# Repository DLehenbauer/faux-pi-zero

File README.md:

# Faux Pi Zero

Open hardware RP2040 dev board in a Raspberry Pi Zero compatible form factor.  Includes Mini HDMI (via [bitbanged DVI](https://github.com/Wren6991/PicoDVI)) and microSD.

## Description

This board aids with migrating a project from the Pi Zero to the RP2040 while retaining the option of moving back to the Pi Zero in the future.  It has the same footprint as the Pi Zero and a partially compatible [pinout](#pinout), making it convenient to support both the RP2040 and Pi Zero in the same design.

## Status

Works, but 1 of 2 boards received by JLCPCB had a solder bridge on the RP2040.  Looking at JLCPCB's EasyEDA footprints, it looks like JLCPCB used longer pads for the RP2040.  I'd recommend using a custom footprint and extending the pads, which hopefully will avoid defects.

A couple other things I'd change in retrospect:
* Expose UART TX/RX on the debug header and reorder pins so you can plug a [picoprobe](https://github.com/raspberrypi/picoprobe) into the board w/o wires.
* Remove the hacky activity LED from the microSD since [the lib](https://github.com/carlk3/no-OS-FatFS-SD-SPI-RPi-Pico) already blinks GP25.
* Try for a 2 layer board to reduce cost
* Reduce buttons to 6 x 3.5 and maybe try to squeeze in an optional wireless module

DVI and microSD both appear to work with a basic test.  I've exercised DVI, USB (host), SPI1, and the debug header quite a bit (all good).  Other functionality is either lightly tested or untested.

## Features

* Compatible footprint:
  * Mini HDMI (via [bitbanged DVI](https://github.com/Wren6991/PicoDVI))
  * Micro SD (via SPI mode.  Cards must be <2TB)
  * Micro USB
  * Power (via Micro USB)
* Partially compatible [pinout](#pinout)
* 16MB Flash
* Green status LED on GP25 (same as Pico)
* Red SD activity LED on GP9
* BOOTSEL and RESET buttons
* SWD Header

## Pinout

See [schematic](#schematic) for more details.

### Mapping from Pi Zero to Faux Px Zero

Pi Pin | Pico Pin | Pi GPIO | Pico GP | Function | Notes
-|-|-|-|-|-
1, 17 | 36 |  | 3V3 (Out) |  |
2, 4 | 39 |  | VSYS |  |
2, 4 | 40 |  | VBUS |  |
3 | 4 | GPIO 02 | GP 02 | I2C_SDA |
5 | 5 | GPIO 03 | GP 03 | I2C_SCL |
6, 9, 14, 20, 25, 30, 34, 39 | 3, 8, 13, 18, 23, 28, 33, 38, DBG-2 |  | GND |  |
7 |  | GPIO 04 | GP 24 |  |
8 | 1 | GPIO 14 | GP 00 | UART0 TX |
10 | 2 | GPIO 15 | GP 01 | UART0 RX |
11 | 12 | GPIO 17 | GP 09 | SD_CSn | Can be used as GP with SD card removed.  Note 10k pullup.
12 | 17 | GPIO 18 | GP 13 | SPI1_CSn | Can be used to share SPI1 with SD card.
13 | 11 | GPIO 27 | GP 08 | SD_DET | Can be used as GP with SD card removed.
15 | 14 | GPIO 22 | GP 10 | DVI_CEC | DVI_CEC when JP3 closed.  See [schematic](#schematic).
16 | 15 | GPIO 23 | GP 11 |  |
18 | DBG-3 | GPIO 24 | SWD |  |
19 | 6/10 | GPIO 10 | GP 04/07 | SPI0_RX/TX | Select [controller](https://www.oshwa.org/a-resolution-to-redefine-spi-signal-names/) or [peripheral](https://www.oshwa.org/a-resolution-to-redefine-spi-signal-names/) via JP1 and JP2.  See [schematic](#schematic).
21 | 10/6 | GPIO 09 | GP 07/04 | SPI0_TX/RX | Select [controller](https://www.oshwa.org/a-resolution-to-redefine-spi-signal-names/) or [peripheral](https://www.oshwa.org/a-resolution-to-redefine-spi-signal-names/) via JP1 and JP2.  See [schematic](#schematic).
22 | DBG-1 | GPIO 25 | SWCLK |  |
23 | 9 | GPIO 11 | GP 06 | SPI0_SCLK |
24 | 7 | GPIO 08 | GP 05 | SPI0_CSn |
26 |  | GPIO 07 |  |  |
27 | 34 | GPIO 00 | GP 28 | I2C_SCL | DVI_SDA when JP4 closed.  See [schematic](#schematic).
28 |  | GPIO 01 | GP 29 |  |
29 | 31 | GPIO 05 | GP 26 |  |
31 | 32 | GPIO 06 | GP 27 | I2C_SDA | DVI_SDA when JP5 closed.  See [schematic](#schematic).
32 |  | GPIO 12 |  |  |
33 |  | GPIO 13 |  |  |
35 | 16 | GPIO 19 | GP 12 | SPI1_RX / SD_DAT | Can be used as GP with SD card removed.  Note 10k pullup.
36 |  | GPIO 16 | BOOTSEL |  |
37 | 30 | GPIO 26 | RUN |  |
38 | 20 | GPIO 20 | GP 15 | SPI1_TX / SD_CMD | Can be used as GP with SD card removed.
40 | 19 | GPIO 21 | GP 14 | SPI1_SCLK / SD_CLK | Can be used as GP with SD card removed.
   |    |    | GP 23 | DVI_D2+ |
   |    | 21 | GP 16 | DVI_CK- |
   |    | 22 | GP 17 | DVI_CK+ |
   |    | 24 | GP 18 | DVI_D0- |
   |    | 25 | GP 19 | DVI_D0+ |
   |    | 26 | GP 20 | DVI_D1- |
   |    | 27 | GP 21 | DVI_D1+ |
   |    | 29 | GP 22 | DVI_D2- |
   | 35 |  | N/C |  |
   | 37 |  | 3V3_EN |  |
   | LED |  | GP 25 |  |

## Schematic

(Click image to view PDF)

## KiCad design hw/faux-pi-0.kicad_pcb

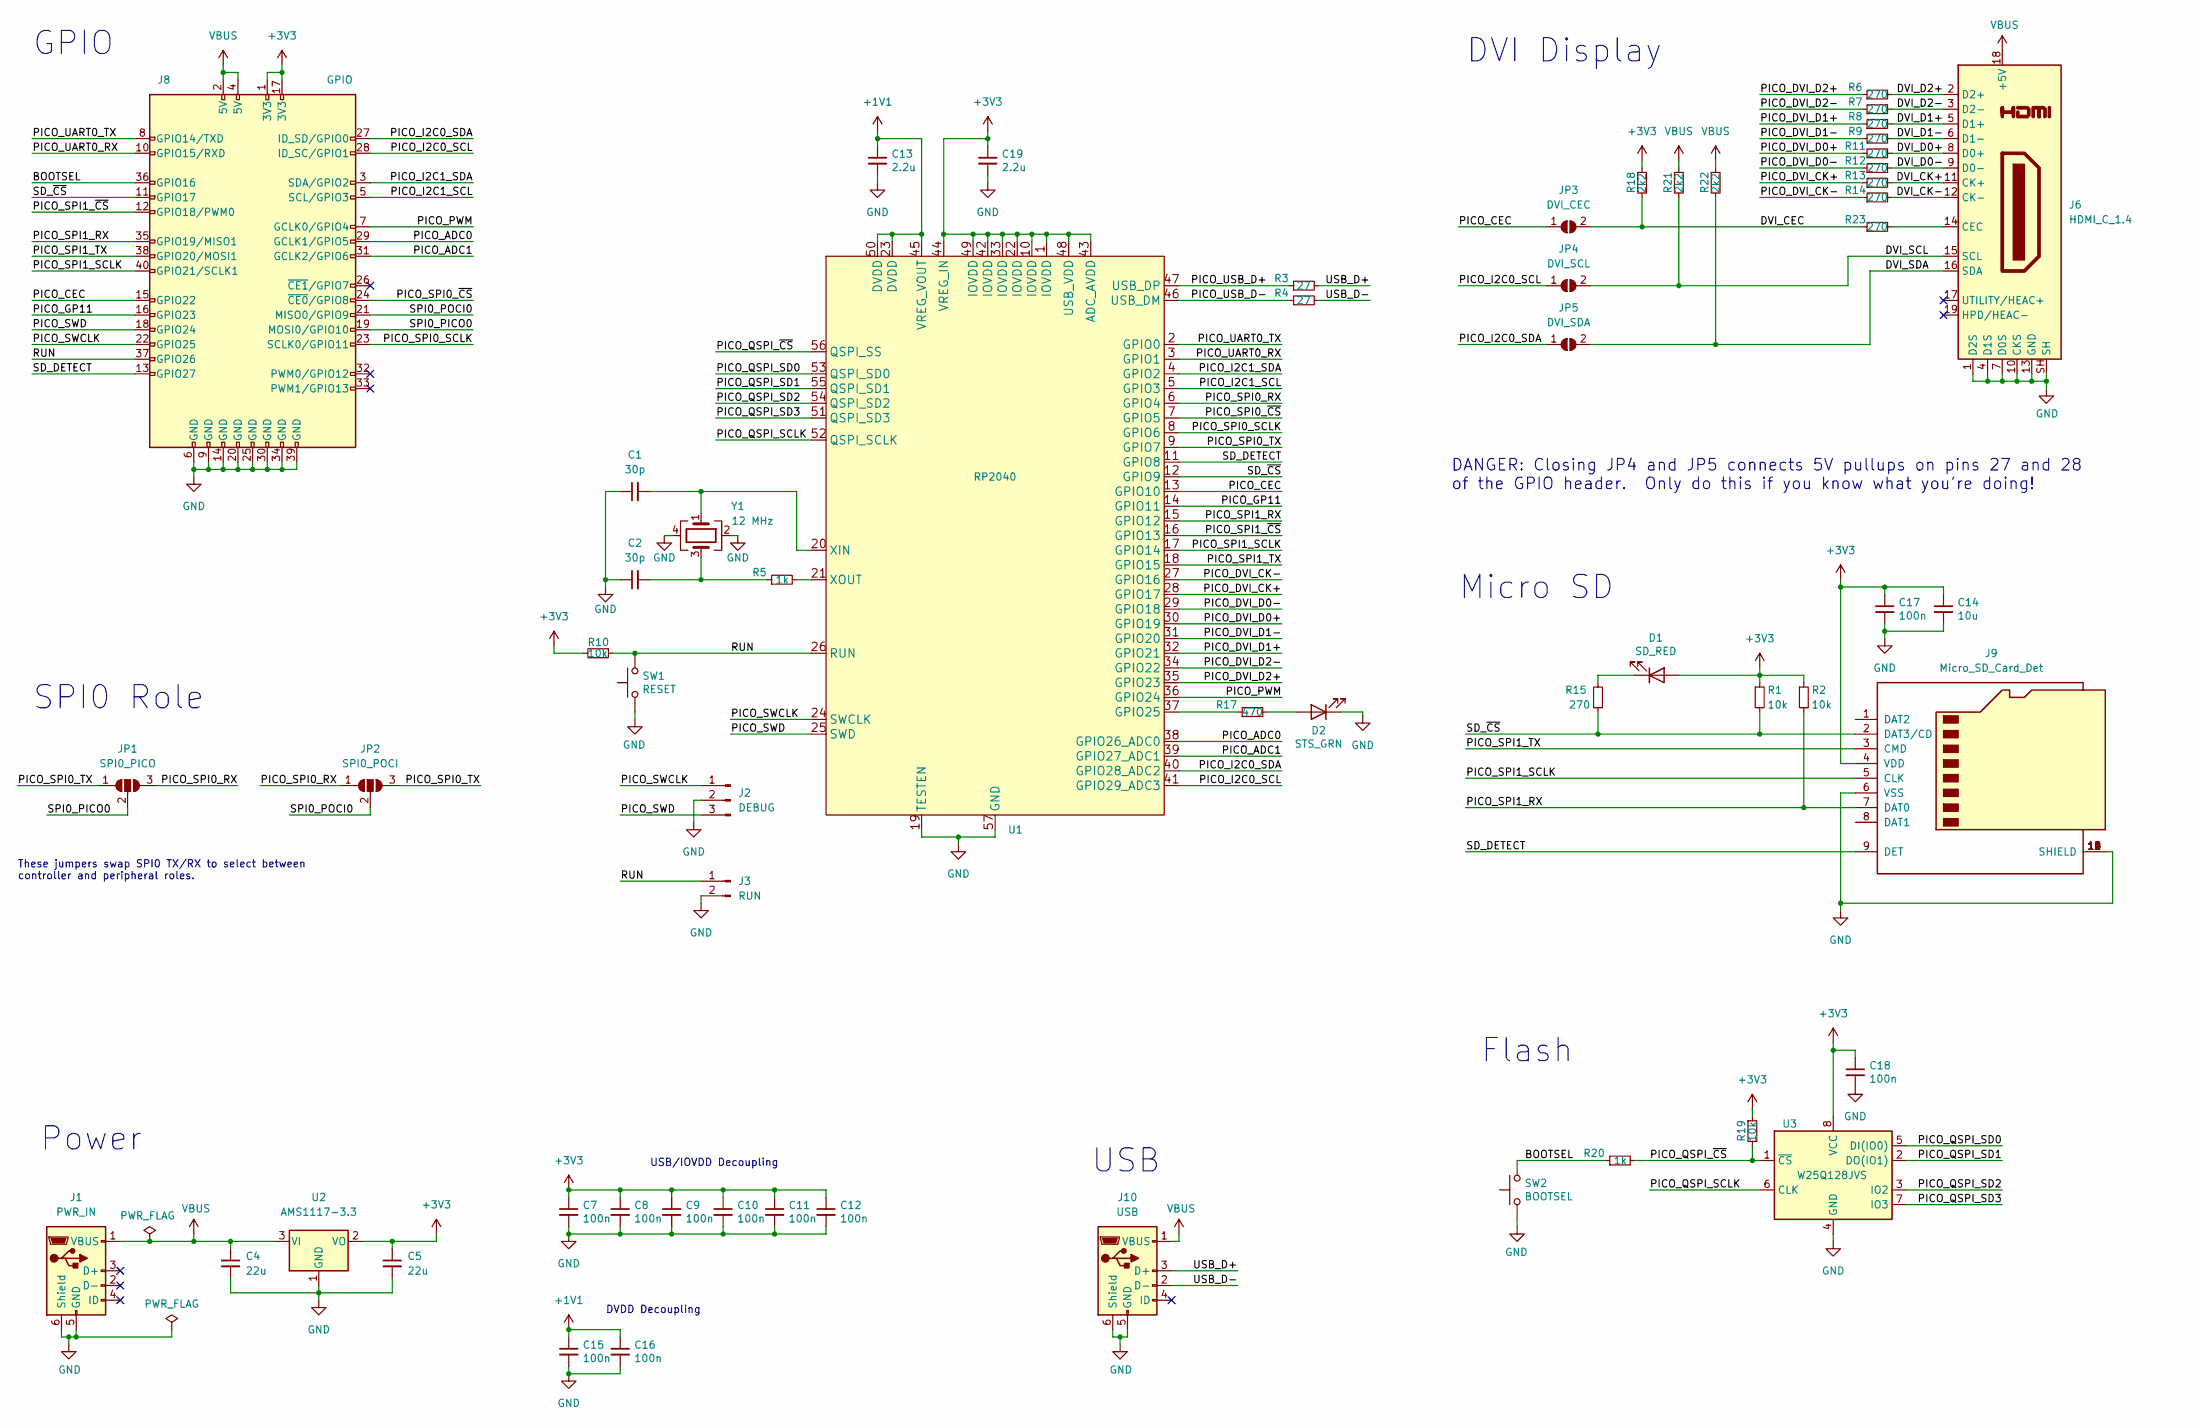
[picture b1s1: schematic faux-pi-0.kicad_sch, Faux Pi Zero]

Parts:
C1, C2: 30p; C_0402_1005Metric; LCSC C1570
C4, C5: 22u; C_0805_2012Metric; LCSC C45783
C7, C8, C9, C10, C11, C12, C15, C16, C17, C18: 100n; C_0402_1005Metric; LCSC C1525
C13, C19: 2.2u; C_0402_1005Metric; LCSC C12530
C14: 10u; C_0402_1005Metric; LCSC C15525
D1: SD_RED; LED_0603_1608Metric; LCSC C2286
D2: STS_GRN; LED_0603_1608Metric; LCSC C72043
J1: PWR_IN; MICRO-USB_MICRO-USB-17; LCSC C77238
J2: DEBUG; PinHeader_1x03_P2.54mm_Vertical
J3: RUN; PinHeader_1x02_P2.54mm_Vertical
J6: HDMI_C_1.4; HDMI-SMD_HDMI-201; LCSC C720618
J8: GPIO; PinHeader_2x20_P2.54mm_Vertical
J9: Micro_SD_Card_Det; SIM-SMD_8P-1040310811; LCSC C585350
J10: USB; MICRO-USB_MICRO-USB-17; LCSC C77238
JP1: SPI0_PICO; SolderJumper-3_P1.3mm_Open_RoundedPad1.0x1.5mm
JP2: SPI0_POCI; SolderJumper-3_P1.3mm_Open_RoundedPad1.0x1.5mm
JP3: DVI_CEC; SolderJumper-2_P1.3mm_Open_RoundedPad1.0x1.5mm
JP4: DVI_SCL; SolderJumper-2_P1.3mm_Open_RoundedPad1.0x1.5mm
JP5: DVI_SDA; SolderJumper-2_P1.3mm_Open_RoundedPad1.0x1.5mm
R1, R2, R10, R19: 10k; R_0402_1005Metric; LCSC C25744
R3, R4: 27; R_0603_1608Metric; LCSC C25190
R5, R20: 1k; R_0402_1005Metric; LCSC C11702
R6, R7, R8, R9, R11, R12, R13, R14, R15, R23: 270; R_0603_1608Metric; LCSC C22966
R17: 470; R_0402_1005Metric; LCSC C25117
R18, R21, R22: 2k2; R_0402_1005Metric; LCSC C25879
SW1: RESET; SW_PUSH_6mm
SW2: BOOTSEL; SW_PUSH_6mm
U1: RP2040; QFN-56-1EP_7x7mm_P0.4mm_EP3.2x3.2mm_ThermalVias; LCSC C2040
U2: AMS1117-3.3; SOT-223-3_TabPin2; LCSC C6186
U3: W25Q128JVS; SOIC-8_5.23x5.23mm_P1.27mm; LCSC C97521
Y1: 12 MHz; Crystal_SMD_3225-4Pin_3.2x2.5mm; LCSC C9002

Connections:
+1V1: C13.1, C15.1, C16.1, U1.23 (DVDD), U1.45 (VREG_VOUT), U1.50 (DVDD)
+3V3: C5.1, C7.1, C8.1, C9.1, C10.1, C11.1, C12.1, C14.1, C17.1, C18.1, C19.1, D1.2 (A), J8.1 (3V3), J8.17 (3V3), J9.4 (VDD), R1.1, R2.1, R10.2, R18.1, R19.1, U1.1 (IOVDD), U1.10 (IOVDD), U1.22 (IOVDD), U1.33 (IOVDD), U1.42 (IOVDD), U1.43 (ADC_AVDD), U1.44 (VREG_IN), U1.48 (USB_VDD), U1.49 (IOVDD), U2.2 (VO), U3.8 (VCC)
/BOOTSEL: J8.36 (GPIO16), R20.1, SW2.2
/DVI_CEC: JP3.2 (B), R18.2, R23.1
/DVI_CK+: J6.11 (CK+), R13.2
/DVI_CK-: J6.12 (CK-), R14.2
/DVI_D0+: J6.8 (D0+), R11.2
/DVI_D0-: J6.9 (D0-), R12.2
/DVI_D1+: J6.5 (D1+), R8.2
/DVI_D1-: J6.6 (D1-), R9.2
/DVI_D2+: J6.2 (D2+), R6.2
/DVI_D2-: J6.3 (D2-), R7.2
/DVI_SCL: J6.15 (SCL), JP4.2 (B), R21.2
/DVI_SDA: J6.16 (SDA), JP5.2 (B), R22.2
/PICO_ADC0: J8.29 (GCLK1/GPIO5), U1.38 (GPIO26_ADC0)
/PICO_ADC1: J8.31 (GCLK2/GPIO6), U1.39 (GPIO27_ADC1)
/PICO_CEC: J8.15 (GPIO22), JP3.1 (A), U1.13 (GPIO10)
/PICO_DVI_CK+: R13.1, U1.28 (GPIO17)
/PICO_DVI_CK-: R14.1, U1.27 (GPIO16)
/PICO_DVI_D0+: R11.1, U1.30 (GPIO19)
/PICO_DVI_D0-: R12.1, U1.29 (GPIO18)
/PICO_DVI_D1+: R8.1, U1.32 (GPIO21)
/PICO_DVI_D1-: R9.1, U1.31 (GPIO20)
/PICO_DVI_D2+: R6.1, U1.35 (GPIO23)
/PICO_DVI_D2-: R7.1, U1.34 (GPIO22)
/PICO_GP11: J8.16 (GPIO23), U1.14 (GPIO11)
/PICO_I2C0_SCL: J8.28 (ID_SC/GPIO1), JP4.1 (A), U1.41 (GPIO29_ADC3)
/PICO_I2C0_SDA: J8.27 (ID_SD/GPIO0), JP5.1 (A), U1.40 (GPIO28_ADC2)
/PICO_I2C1_SCL: J8.5 (SCL/GPIO3), U1.5 (GPIO3)
/PICO_I2C1_SDA: J8.3 (SDA/GPIO2), U1.4 (GPIO2)
/PICO_PWM: J8.7 (GCLK0/GPIO4), U1.36 (GPIO24)
/PICO_QSPI_SCLK: U1.52 (QSPI_SCLK), U3.6 (CLK)
/PICO_QSPI_SD0: U1.53 (QSPI_SD0), U3.5 (DI(IO0))
/PICO_QSPI_SD1: U1.55 (QSPI_SD1), U3.2 (DO(IO1))
/PICO_QSPI_SD2: U1.54 (QSPI_SD2), U3.3 (IO2)
/PICO_QSPI_SD3: U1.51 (QSPI_SD3), U3.7 (IO3)
/PICO_QSPI_~CS: R19.2, R20.2, U1.56 (QSPI_SS), U3.1 (~CS)
/PICO_SPI0_RX: JP1.3 (B), JP2.1 (A), U1.6 (GPIO4)
/PICO_SPI0_SCLK: J8.23 (SCLK0/GPIO11), U1.8 (GPIO6)
/PICO_SPI0_TX: JP1.1 (A), JP2.3 (B), U1.9 (GPIO7)
/PICO_SPI0_~CS: J8.24 (~CE0/GPIO8), U1.7 (GPIO5)
/PICO_SPI1_RX: J8.35 (GPIO19/MISO1), J9.7 (DAT0), R2.2, U1.15 (GPIO12)
/PICO_SPI1_SCLK: J8.40 (GPIO21/SCLK1), J9.5 (CLK), U1.17 (GPIO14)
/PICO_SPI1_TX: J8.38 (GPIO20/MOSI1), J9.3 (CMD), U1.18 (GPIO15)
/PICO_SPI1_~CS: J8.12 (GPIO18/PWM0), U1.16 (GPIO13)
/PICO_SWCLK: J2.1, J8.22 (GPIO25), U1.24 (SWCLK)
/PICO_SWD: J2.3, J8.18 (GPIO24), U1.25 (SWD)
/PICO_UART0_RX: J8.10 (GPIO15/RXD), U1.3 (GPIO1)
/PICO_UART0_TX: J8.8 (GPIO14/TXD), U1.2 (GPIO0)
/PICO_USB_D+: R3.1, U1.47 (USB_DP)
/PICO_USB_D-: R4.1, U1.46 (USB_DM)
/RUN: J3.1, J8.37 (GPIO26), R10.1, SW1.2, U1.26 (RUN)
/SD_DETECT: J8.13 (GPIO27), J9.9 (DET), U1.11 (GPIO8)
/SD_~CS: J8.11 (GPIO17), J9.2 (DAT3/CD), R1.2, R15.1, U1.12 (GPIO9)
/SPI0_PICO0: J8.19 (MOSI0/GPIO10), JP1.2 (C)
/SPI0_POCI0: J8.21 (MISO0/GPIO9), JP2.2 (C)
/USB_D+: J10.3 (D+), R3.2
/USB_D-: J10.2 (D-), R4.2
GND: C1.1, C2.1, C4.2, C5.2, C7.2, C8.2, C9.2, C10.2, C11.2, C12.2, C13.2, C14.2, C15.2, C16.2, C17.2, C18.2, C19.2, D2.1 (K), J1.5 (GND), J1.6 (Shield), J2.2, J3.2, J6.1 (D2S), J6.4 (D1S), J6.7 (D0S), J6.10 (CKS), J6.13 (GND), J6.SH, J8.6 (GND), J8.9 (GND), J8.14 (GND), J8.20 (GND), J8.25 (GND), J8.30 (GND), J8.34 (GND), J8.39 (GND), J9.6 (VSS), J9.10 (SHIELD), J9.11 (SHIELD), J9.12 (SHIELD), J9.13 (SHIELD), J9.14 (SHIELD), J10.5 (GND), J10.6 (Shield), SW1.1, SW2.1, U1.19 (TESTEN), U1.57 (GND), U2.1 (GND), U3.4 (GND), Y1.2, Y1.4
unnamed: C1.2, U1.20 (XIN), Y1.1
unnamed: C2.2, R5.1, Y1.3
unnamed: D1.1 (K), R15.2
unnamed: D2.2 (A), R17.2
unnamed: J6.14 (CEC), R23.2
unnamed: R5.2, U1.21 (XOUT)
unnamed: R17.1, U1.37 (GPIO25)
VBUS: C4.1, J1.1 (VBUS), J6.18 (+5V), J8.2 (5V), J8.4 (5V), J10.1 (VBUS), R21.1, R22.1, U2.3 (VI)

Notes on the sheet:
These jumpers swap SPI0 TX/RX to select between controller and peripheral roles.
DANGER: Closing JP4 and JP5 connects 5V pullups on pins 27 and 28 of the GPIO header. Only do this if you know what you're doing!
USB/IOVDD Decoupling
Flash
USB
GPIO
SPI0 Role
DVI Display
DVDD Decoupling
Power
Micro SD

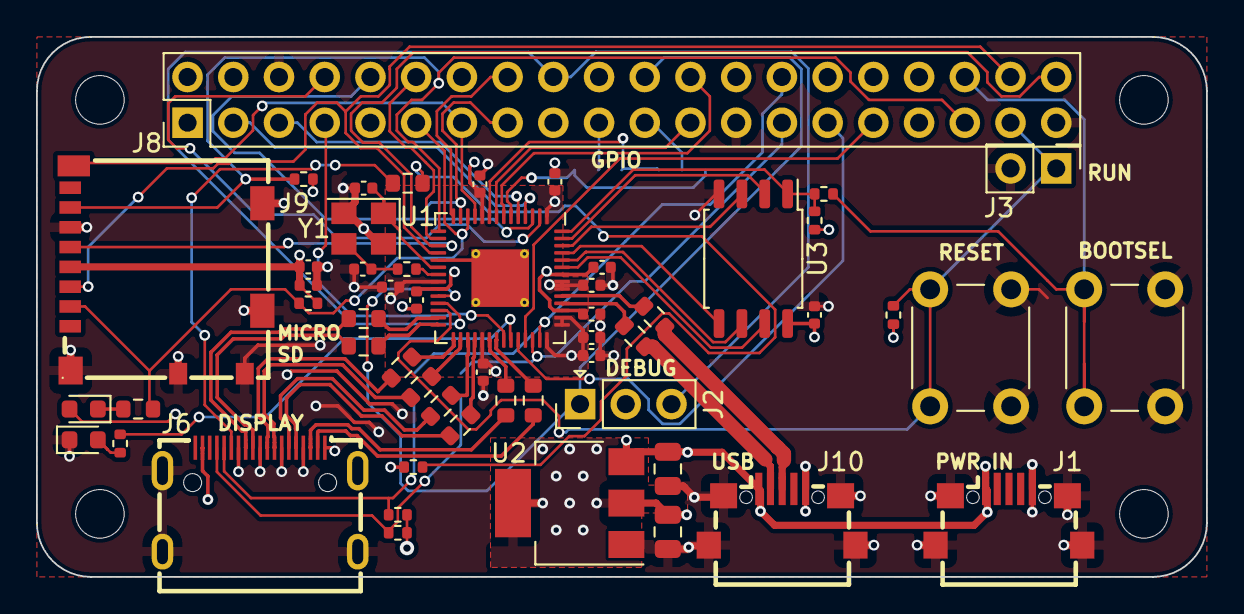
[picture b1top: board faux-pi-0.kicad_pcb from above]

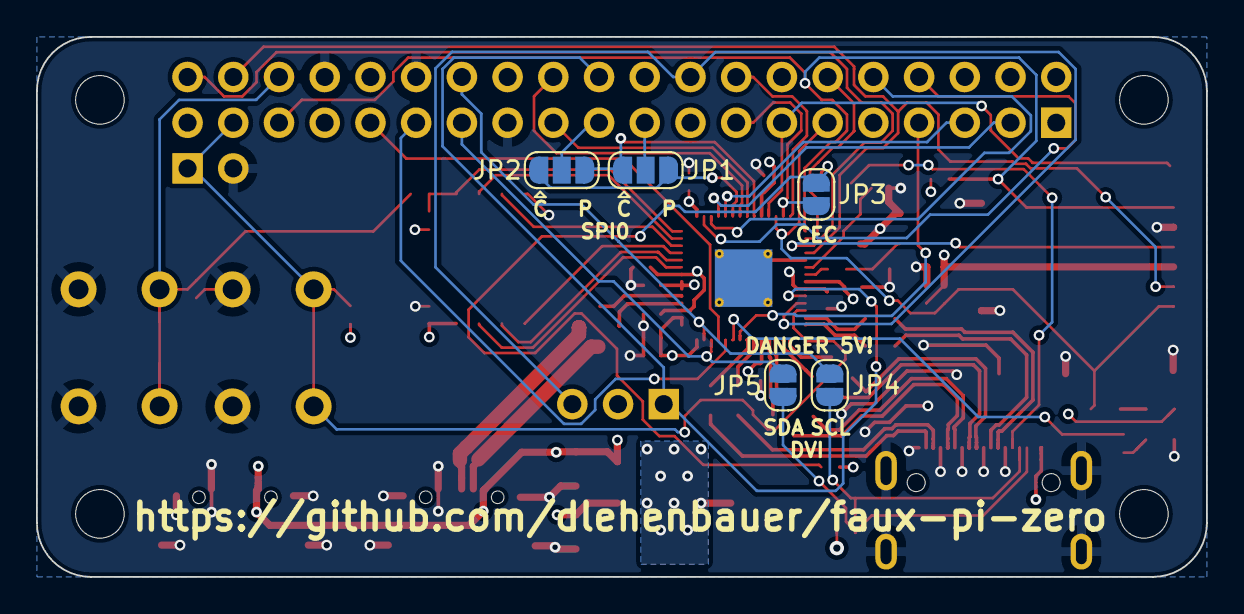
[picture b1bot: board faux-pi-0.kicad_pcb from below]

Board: 4 copper layers, 65.0 x 30.0 mm, 63 parts (5 on the bottom side), 67 nets.

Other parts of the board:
MH1, MH2, MH3, MH4: MountingHole_2.7mm_M2.5

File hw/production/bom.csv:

Designator,Footprint,Quantity,Value,LCSC Part #
"C1, C2",C_0402_1005Metric,2,30p,C1570
"C10, C11, C12, C15, C16, C17, C18, C7, C8, C9",C_0402_1005Metric,10,100n,C1525
"C13, C19",C_0402_1005Metric,2,2.2u,C12530
C14,C_0402_1005Metric,1,10u,C15525
"C4, C5",C_0805_2012Metric,2,22u,C45783
D1,LED_0603_1608Metric,1,SD_RED,C2286
D2,LED_0603_1608Metric,1,STS_GRN,C72043
J1,MICRO-USB_MICRO-USB-17,1,PWR_IN,C77238
J10,MICRO-USB_MICRO-USB-17,1,USB,C77238
J2,PinHeader_1x03_P2.54mm_Vertical,1,DEBUG,
J3,PinHeader_1x02_P2.54mm_Vertical,1,RUN,
J6,HDMI-SMD_HDMI-201,1,HDMI_C_1.4,C720618
J8,PinHeader_2x20_P2.54mm_Vertical,1,GPIO,
J9,SIM-SMD_8P-1040310811,1,Micro_SD_Card_Det,C585350
JP1,SolderJumper-3_P1.3mm_Open_RoundedPad1.0x1.5mm,1,SPI0_PICO,
JP3,SolderJumper-3_P1.3mm_Open_RoundedPad1.0x1.5mm,1,SPI0_POCI,
JP7,SolderJumper-2_P1.3mm_Open_RoundedPad1.0x1.5mm,1,DVI_CEC,
JP8,SolderJumper-2_P1.3mm_Open_RoundedPad1.0x1.5mm,1,DVI_SCL,
JP9,SolderJumper-2_P1.3mm_Open_RoundedPad1.0x1.5mm,1,DVI_SDA,
"R1, R10, R19, R2",R_0402_1005Metric,4,10k,C25744
"R11, R12, R13, R14, R15, R23, R6, R7, R8, R9",R_0603_1608Metric,10,270,C22966
R17,R_0402_1005Metric,1,470,C25117
"R18, R21, R22",R_0402_1005Metric,3,2k2,C25879
"R20, R5",R_0402_1005Metric,2,1k,C11702
"R3, R4",R_0603_1608Metric,2,27,C25190
SW1,SW_PUSH_6mm,1,RESET,
SW2,SW_PUSH_6mm,1,BOOTSEL,
U1,QFN-56-1EP_7x7mm_P0.4mm_EP3.2x3.2mm_ThermalVias,1,RP2040,C2040
U2,SOT-223-3_TabPin2,1,AMS1117-3.3,C6186
U3,SOIC-8_5.23x5.23mm_P1.27mm,1,W25Q128JVS,C97521
Y1,Crystal_SMD_3225-4Pin_3.2x2.5mm,1,12 MHz,C9002

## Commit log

2022-12-10 routed
2022-12-11 Expose BOOTSEL and RUN on GPIO header
2022-12-11 wip: README
2022-12-11 docs & remove UART jumpers
2022-12-11 Add production files for JLCPCB
2022-12-12 tweaks
2022-12-24 README: Fix link to pinout.svg
2022-12-24 .gitignore, rm jlcpcb-import.ps1
2022-12-24 Update pinout
